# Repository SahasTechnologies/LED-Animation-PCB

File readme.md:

# PCB Blinker
This is an animated PCB with LEDs that turn on in different patterns by using the three multivibrators below. 

### [Bistable Multivibrator](https://falstad.com/circuit/circuitjs.html?ctz=CQAgjCAMB0l3BWcMBMcUHYMGZIA4UA2ATmIxAUgpABZsKBTAWjDACgAlEYw73sXjyjCaVJFQnQEbAO595NGnnmQ2AJ1pKFWsBl5UwcdfKFDd+5KoEp55kNht2bAEwYAzAIYBXADYAXJh8GZ3BhSUh2a01lOwQwRz0QF3dvf0Dg0IkoWHYAc3sE3gdwYhsJNny4wop4krKoY0UYxOxsfkSDeGMzRJQUGnAOy1U5VvbePoHMMtkk-sGitqSMGb97Jeno5fqIJhhsPAJIUkIaXTpD-WgSSDQiQhIDyEIMYksQV09fPzY1ye35JsDCA9tADkcTmcMGcEFgrjc7g9HnhnsQYnAPilvrMeoIJgh9LMmgstigCQ18sSUIctg4sqp8kJqcohHSwsZ-pt-qIsoYjBoxgDBTzhHzVFxiSLidgEPUqKJqPSpJwFBjWbKwrQxJqYNIAM6qqjcjHAvxqLwMNgG4UYyUm0Jmi1sUT0GhM+aEebM4QIAD6p19kF9olIvrA0DJgdg8DIhAJkZYvpQvr92GdkHoTC0aGUKIB8v9NEDweOxDDEb9MHgxz08b9ieTRbTLpB2ZpeZlO2whf9JbRSakUbAvsT7BbbqKkAGnoGbWUBmTAcIfbw5cjMGHo7YQA)

### [Astable Multivibrator](https://falstad.com/circuit/circuitjs.html?ctz=CQAgjCAMB0l3BWcMBMcUHYMGZIA4UA2ATmIxAUgpABZsKBTAWjDACgAlcGmkPKmnj5URtKklEwEbAE7de-eeAyEoIbLlkhMKYdoy6wKtWHhaacPRapHVNswHclinXshsnrxdbdaEKIUV-IVs1bDQPMSoggN8AY31DYzAeZVVeGHg4UhzcvNIQJhgUsACUYgQ8DBoEUirdTMgIdwSfUOC02ihYLPy+nMKwaAxWcsIMBBoJmkINIUbmtgAXWmJVAKEOjZNClGhBDGJIXDwwPGDYqUhxtCqwQjQsPHpTKgATBgAzAEMAVwAbJbLTrbFK8bY2bqzBDhDSEZ7+MAVCTQcYIGEESBTbBrSZIV4gD4-AFApxgzrk1zuJwddqxKmRGhrbR4IQ+CGRVyhdmsqCMyyhVwczwGFkhYwc+66Dq4Xgy+HaQlfP6Apj-BhvcBqESwdhSpSyg0K3RElVLNUarWSXVsADmRpCqWweAyfPt8s2sWdrvcQA)

### [Monostable Multivibrator](https://falstad.com/circuit/circuitjs.html?ctz=CQAgjCAMB0l3BWcMBMcUHYMGZIA4UA2ATmIxAUgpABZsKBTAWjDACgAlWvEQmkJthS9+VKjSpIxUaAjYB3biPCEqfKApVr+KPD3WRNu-fwSrlhgE5L1NHmBqjkcNtbDn17qg6dh4rkGNlIJ8oZysKD1NzUO9-AGMtQPxAvWSeUVh4SFJcvPzSWmhsbBwEbEJ3PD4aMpk4CENFL3BHJLQeJtT7NqCOjQAXCl0QIUlzMbDG6EIhDEgaHwRiZbwcGUJCIhoEPGISyBKa5xAAEwYAMwBDAFcAGwG2IbBiYUmWye8BGmgyRCwzNg1sRFgIYA5KoczLp9igUKx7HAzpdbg8nuARu8Jmgpt8ZpAEChsAgwNgXpAyoQZPC1uTKrscHwEOQ-FRztd7o9muZ+h8FhoAM5KUJ2UY4r4DSw3BiaUXvTHioxpfoSKifWVIyaEnjqxRmbxtfXpDTWI0qpH9OIuRSq41BXXdMXeV5OjTuYQfCpJW3CdmogZMO4MU7gMJiWDsADm3qRLTowjEmjNKSNuFEbGjqa9qbwTkMQA)

## Here is what I created in [Falstad](https://falstad.com/circuit/circuitjs.html?ctz=CQAgjCAMB0l3BWcMBMcUHYMGZIA4UA2ATmIxAUgpABZsKBTAWjDACgAlKEQm77FNyo0qSKuOgI2Adx59e4GvL6QZi5SEyCFq2VrkhseDbsPGDNPFR1sATgYUKwS7mHh31B532+v39-QV9Xyo3OA8jDUjPUP9aKwsEkORwgBdDQTBCax9s1yhJEmxCFDwsODBSBDwCkpoiYuJLUmIwDEIUkAATBgAzAEMAVwAbVLZ04g6s0Jdp-KYYEsq8LMqwFBpCbAECyjBsGiyEerIENGJOnoGRsfS0GrngvNDa-AxISna8QhIfjsXsFVsmBvpFLBAwt0+kNRuMMqE8tE5i8FtBst8aAhCBg8C1IJZBDBKIdLAhnMZsRhiEhIVcYbdaDs5pYEeJwK9vhg0AgqQhsDjLLVAcQjKKBJySJdoTc2FlBCzwO14lR7pooddRkxhgwuuy2TBIOw5WYfEroqrBHSblqdXqhLAjSVNFzFR19Bb1fSbbqIPqHbKnb42lMXB6rZrtT6hAVDQHtKaOkF8Grw6lvXaJLGAOYGVVBDZCNg593J90F8RFk2aZPm8tQSsK1WNuuqHO+VXtltqJnPcDPNSs7goLH12ROFyTGJqSe+Gf92RB0PJkJqDtLh7z52ZFwCGYqbtoTy7vsV2RIlx0bf72SXzy35FsADGIDnVEnw46Klg8Eg5FRWJFEoyneQ0qhqA1DXrZ8OzyC0Ry-H9fxjM5CBBDB6nWBocEnCDfSfeETwIj9aBjH8-yJLF8C2A50MvYhCW-PDn3vPJb2IhCyOQ4cEBFJRhxoDAQTIf5GNHIcR3fEdTEkt1Syk1c5I6Y9iNMZT4J2FS1DYkczhqTTn10wjDPY0j4HIyQsVYTB9hIYhIEIapSLw2RDN8VzNwVNzSinHMeVkmo-M0LtjUC4MKCVMNpQjW1fXtWN0nc0QlWRdlUXRbEUFWFBtgc1DdnxZwUBFKk6F-GgLlpKKxnsQKFFClxYnCG8EjqpUbBc7ziLqTR5Ofbq5m6kyILMriEB4pQMD5TE7PoXCxP6lx+s3er5ALFccwy6sak2lBgqdTawp20tPWtSMMxjdh0iW6wXRS300SorlWG+ISsnAtFhUiZwqTKQ4KrgE7YXsTbHFuhqUlMWr5BdGxny5Qd4Z6z9TLgcyxtQ9ZsTcYwBAcpyxMR3xCc3A6XEJhrKy+LaQCp3aVHrY0qbC2njtTdNYszS6acPOYmd7CA0sezKQT8klZskAqTk2akNjxyqNWqmnCG2vgmfBsJTBB1XlYMUwqYUDFdY8Q2DfHemNbhFYpjyQ27o5DLnrG9CirED7SC+gT2neSapQVuMQFtpVDcihX2ejA12BzYPk2DrtZDVvgranWQk98VP+2fdOqCTobvxGg0zjGpoBPK+4cVdioxJNvhJhyet7FrgxG+SC2JnWQjm-5kBBc5XbWGpbYCvykkiulrEBPMeX6X95ulUbkOvTOjmLsrefk3nuOA7Nl925XWRWivHfMgzo+O-b3PELRyzMcE+yprafHVGfMIN0avT4JRpCC+46kRDwMpJgbA4s5FIDxZhwFfmJZu4DlwUzbB8fyyARx00LMaNwI4wroMQZaKqYc-TxVAYRLBhEXiLCFt4OgglcBfi2O7HG2RMBbE2L7ae9hiFOAQTECG048gcJHLDcAbhcihCEUjEiw1UbdwohjIgkBsDHFaNiC4c1TCsHxJ4NRwixLEKDKI9agizjU1YIYlBFY0FgEMZgixggF6nRiuHf06RNFEOsSQ1KZCygHBILiOo-8GLEkKpMdYuB5H0RYTKNhrinCuJbu4BcnDomGIEesAGcwUkqg-hIr+sAUK7UgL-fYu5xaV1UWgPc4AykkLUMYw+6SfIVMFB2DYek9qZGaa6BpelWa4KXg4ghdS0ntLth45WTR2huHkbwBitCZY-DspAD8-0qCpg8OsQUTghnqziQY+MnSjbPyKtbUIhyxEcRGv+Si2IjD2TshsQEj9qknKDE8zcaywE+CeXA8ABw+Adh+UFemqg0H-Mwf82x0Uoz4K5usV83zZhd1RDiMpw5iArHkVgZhRICqF0yriaoTRMgAxWWw-5TgQVbKanssli19zP0BMfUI9LTmf3IKgFF8jMq0TGrgVlolVFMqDAK155KfACq+d4FUsCRAAtQYGJQoRkryupjg0OvSoVwn2GEtJSrhnQF2jxDlbQlDcuyXMgQPIcCYlxfUcJQN1B1wlVwi2C5SU+CVe1HgBZiKI00vHQ8xEc7yRTlkMRB8xHSXPhgiB4bqnRuIs431gj1HxsqYmupKaZLaJOfGplabc0YOJDGhchb42Fr3uAMtswdUUwAM7cEcCYbgAxhg1oYGwIAA):

This uses transistors to turn the LEDs on and off in different patterns to create a ring oscillator. I uses NPN Transistors, capacitors, resistors and LEDs to make this aniamation.

### PCB
This is how the PCB looks! 

I created a circular array in KiCad to make it look  aaesthetic and the pattern to look like it is repeating forever.

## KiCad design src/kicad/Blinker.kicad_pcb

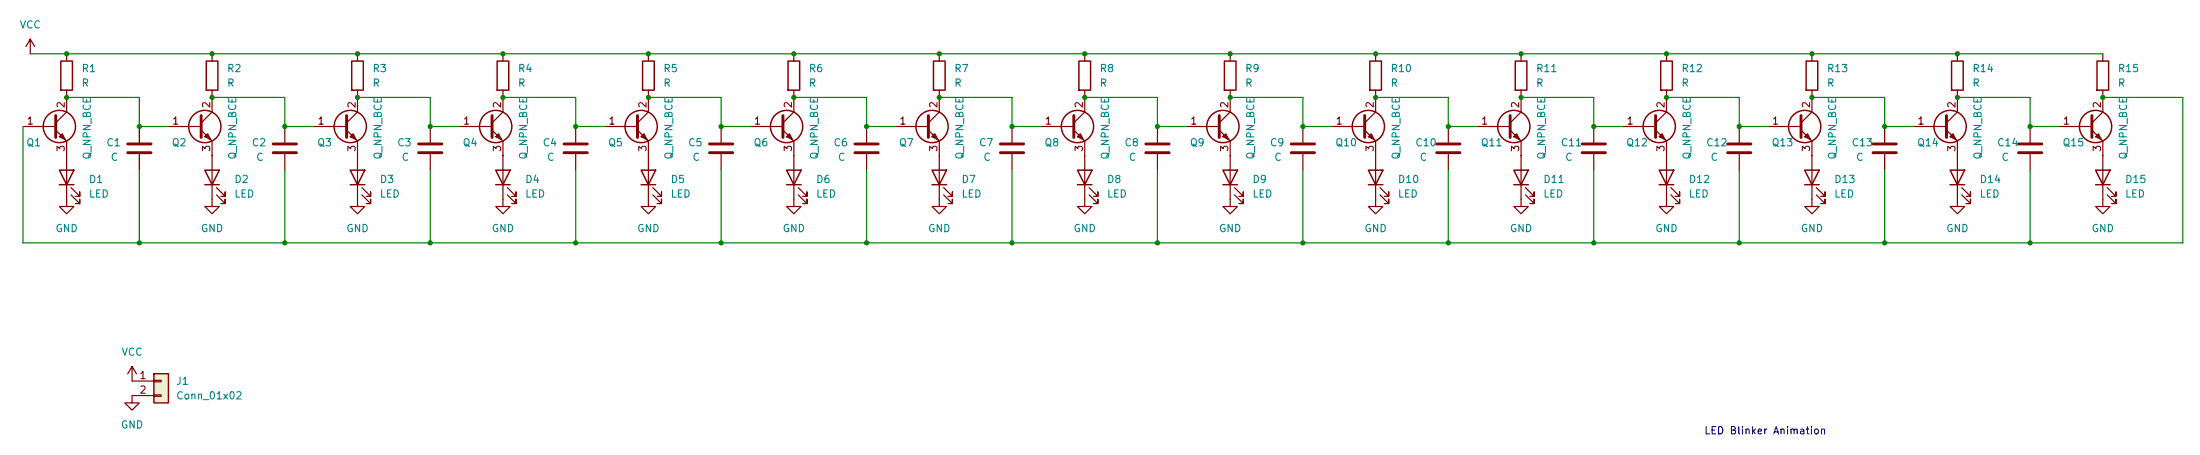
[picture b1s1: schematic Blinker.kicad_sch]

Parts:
C1, C2, C3, C4, C5, C6, C7, C8, C9, C10, C11, C12, C13, C14: C; C_Disc_D5.0mm_W2.5mm_P5.00mm
D1, D2, D3, D4, D5, D6, D7, D8, D9, D10, D11, D12, D13, D14, D15: LED; LED_D5.0mm
J1: Conn_01x02; PinHeader_1x02_P2.54mm_Vertical
Q1, Q2, Q3, Q4, Q5, Q6, Q7, Q8, Q9, Q10, Q11, Q12, Q13, Q14, Q15: Q_NPN_BCE; TO-92L_Inline_Wide
R1, R2, R3, R4, R5, R6, R7, R8, R9, R10, R11, R12, R13, R14, R15: R; R_Axial_DIN0204_L3.6mm_D1.6mm_P7.62mm_Horizontal

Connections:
GND: D1.1 (K), D2.1 (K), D3.1 (K), D4.1 (K), D5.1 (K), D6.1 (K), D7.1 (K), D8.1 (K), D9.1 (K), D10.1 (K), D11.1 (K), D12.1 (K), D13.1 (K), D14.1 (K), D15.1 (K), J1.2
unnamed: D1.2 (A), Q1.3 (E)
unnamed: D2.2 (A), Q2.3 (E)
unnamed: D3.2 (A), Q3.3 (E)
unnamed: D4.2 (A), Q4.3 (E)
unnamed: D5.2 (A), Q5.3 (E)
unnamed: D6.2 (A), Q6.3 (E)
unnamed: D7.2 (A), Q7.3 (E)
unnamed: D8.2 (A), Q8.3 (E)
unnamed: D9.2 (A), Q9.3 (E)
unnamed: D10.2 (A), Q10.3 (E)
unnamed: D11.2 (A), Q11.3 (E)
unnamed: D12.2 (A), Q12.3 (E)
unnamed: D13.2 (A), Q13.3 (E)
unnamed: D14.2 (A), Q14.3 (E)
unnamed: D15.2 (A), Q15.3 (E)
unnamed 16: C1.2, C2.2, C3.2, C4.2, C5.2, C6.2, C7.2, C8.2, C9.2, C10.2, C11.2, C12.2, C13.2, C14.2, Q1.1 (B), Q15.2 (C), R15.2; also elsewhere on the board
unnamed 17: C1.1, Q1.2 (C), Q2.1 (B), R1.2; also elsewhere on the board
unnamed: C2.1, Q2.2 (C), Q3.1 (B), R2.2
unnamed: C3.1, Q3.2 (C), Q4.1 (B), R3.2
unnamed: C4.1, Q4.2 (C), Q5.1 (B), R4.2
unnamed: C5.1, Q5.2 (C), Q6.1 (B), R5.2
unnamed: C6.1, Q6.2 (C), Q7.1 (B), R6.2
unnamed: C7.1, Q7.2 (C), Q8.1 (B), R7.2
unnamed: C8.1, Q8.2 (C), Q9.1 (B), R8.2
unnamed: C9.1, Q9.2 (C), Q10.1 (B), R9.2
unnamed: C10.1, Q10.2 (C), Q11.1 (B), R10.2
unnamed: C11.1, Q11.2 (C), Q12.1 (B), R11.2
unnamed: C12.1, Q12.2 (C), Q13.1 (B), R12.2
unnamed: C13.1, Q13.2 (C), Q14.1 (B), R13.2
unnamed: C14.1, Q14.2 (C), Q15.1 (B), R14.2
VCC: J1.1, R1.1, R2.1, R3.1, R4.1, R5.1, R6.1, R7.1, R8.1, R9.1, R10.1, R11.1, R12.1, R13.1, R14.1, R15.1

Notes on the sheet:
LED Blinker Animation

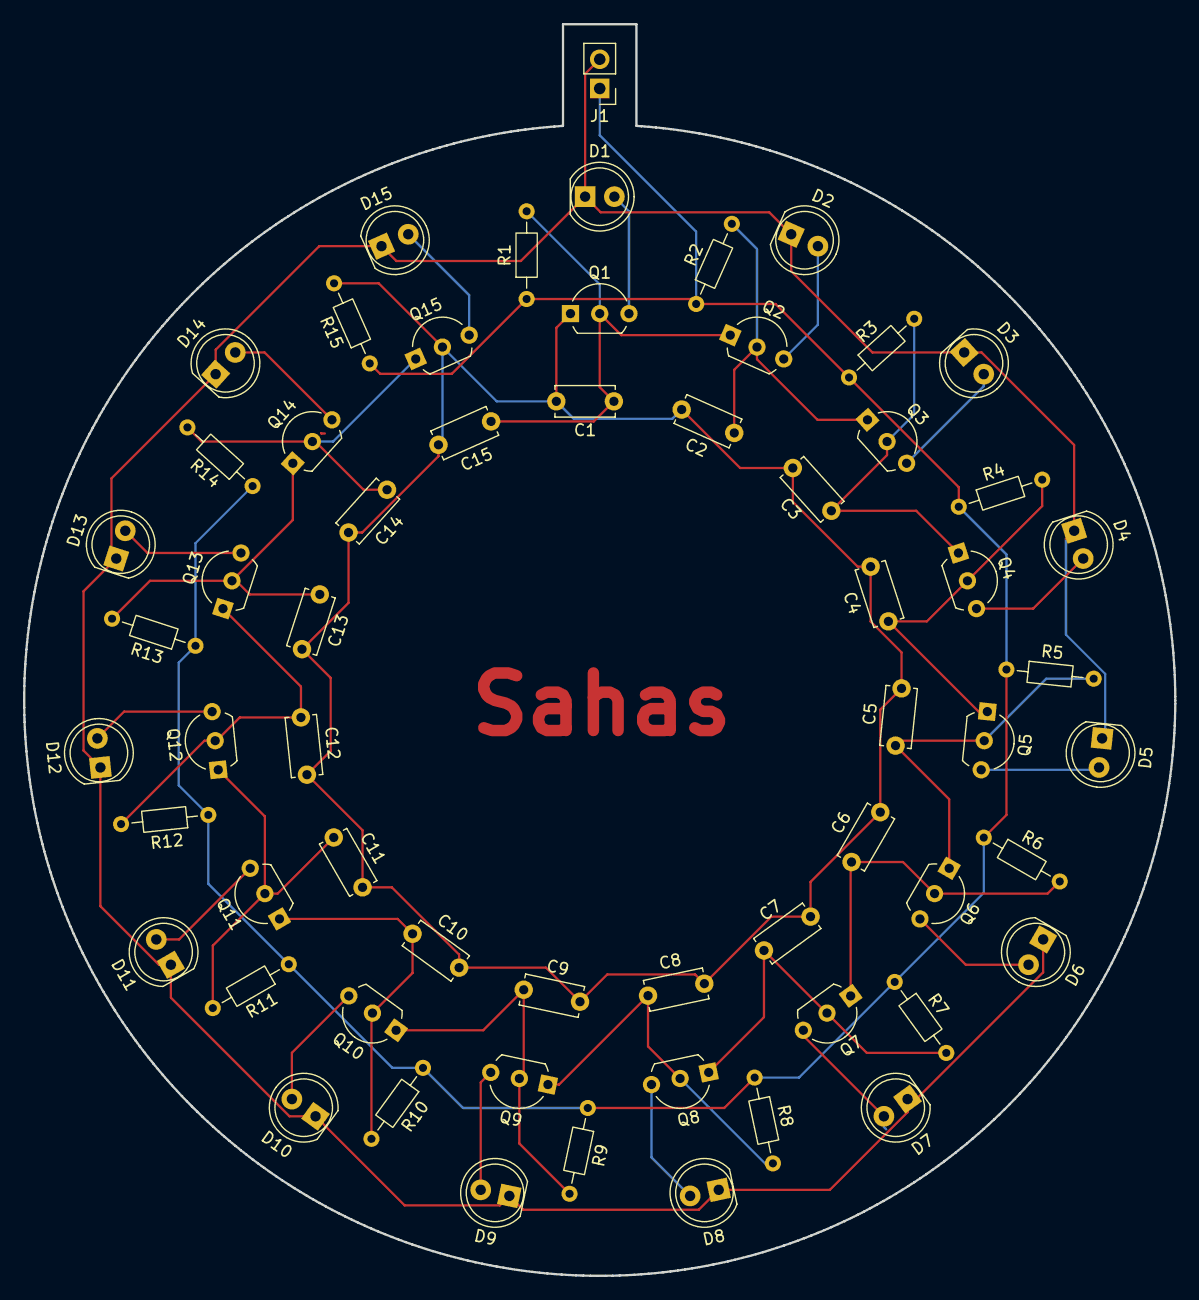
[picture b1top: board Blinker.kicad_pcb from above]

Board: 2 copper layers, 100.0 x 108.7 mm, 61 parts (0 on the bottom side), 32 nets.

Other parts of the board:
C15: C; C_Disc_D5.0mm_W2.5mm_P5.00mm

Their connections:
unnamed 16: C15.2; also elsewhere on the board
unnamed 17: C15.1; also elsewhere on the board

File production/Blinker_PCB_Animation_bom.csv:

Designator,Footprint,Quantity,Value,LCSC Part #
"C1, C10, C11, C12, C13, C14, C15, C2, C3, C4, C5, C6, C7, C8, C9",C_Disc_D5.0mm_W2.5mm_P5.00mm,15,C,
"D1, D10, D11, D12, D13, D14, D15, D2, D3, D4, D5, D6, D7, D8, D9",LED_D5.0mm,15,LED,
J1,PinHeader_1x02_P2.54mm_Vertical,1,Conn_01x02,
"Q1, Q10, Q11, Q12, Q13, Q14, Q15, Q2, Q3, Q4, Q5, Q6, Q7, Q8, Q9",TO-92L_Inline_Wide,15,Q_NPN_BCE,
"R1, R10, R11, R12, R13, R14, R15, R2, R3, R4, R5, R6, R7, R8, R9",R_Axial_DIN0204_L3.6mm_D1.6mm_P7.62mm_Horizontal,15,R,

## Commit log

2026-03-25 Started learning about Multivibrators
2026-03-25 Replace images with mp4 recordings in readme
    Updated images in the readme to use new mp4 recordings.
2026-03-27 Upload all the files
2026-03-27 Enhance README with images and PCB details
    Added images and improved PCB description in README.
